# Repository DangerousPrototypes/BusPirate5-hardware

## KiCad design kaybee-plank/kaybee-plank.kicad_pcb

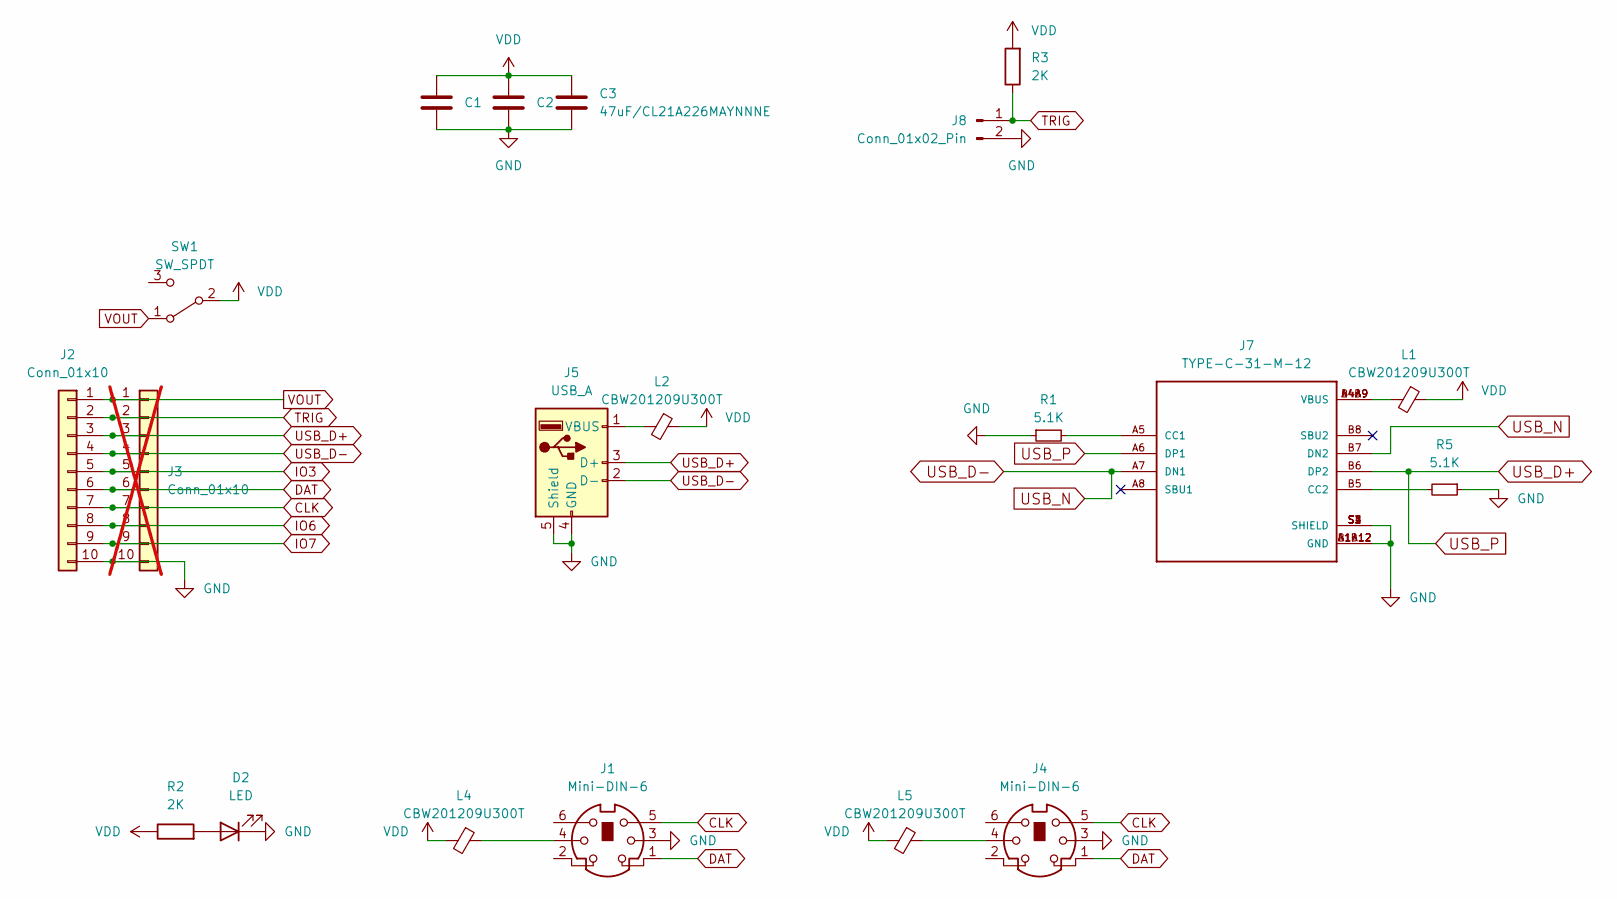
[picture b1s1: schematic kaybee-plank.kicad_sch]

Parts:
C1, C2, C3: 47uF/CL21A226MAYNNNE; C_0805_2012Metric
D2: LED; LED_0805_2012Metric
J1, J4: Mini-DIN-6; Connector_Mini-DIN_Female_6Pin_2rows
J2: Conn_01x10; PinSocket_1x10_P2.54mm_Horizontal
J3: Conn_01x10; PinHeader_1x10_P2.54mm_Vertical; not fitted
J5: USB_A; USB_A_CONNFLY_DS1095-WNR0
J7: TYPE-C-31-M-12; HRO_TYPE-C-31-M-12
J8: Conn_01x02_Pin; PinHeader_1x02_P2.54mm_Vertical
L1, L2, L4, L5: CBW201209U300T; L_0805_2012Metric
R1, R5: 5.1K; R_0805_2012Metric
R2, R3: 2K; R_0805_2012Metric
SW1: SW_SPDT; SW_SPDT_PCM12

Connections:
CLK: J1.5, J2.7, J3.7, J4.5
DAT: J1.1, J2.6, J3.6, J4.1
GND: C1.2, C2.2, C3.2, D2.1 (K), J1.3, J2.10, J3.10, J4.3, J5.4 (GND), J5.5 (Shield), J7.A1B12 (GND), J7.B1A12 (GND), J7.S1 (SHIELD), J7.S2 (SHIELD), J7.S3 (SHIELD), J7.S4 (SHIELD), J8.2, R1.1, R5.1
IO3: J2.5, J3.5
IO6: J2.8, J3.8
IO7: J2.9, J3.9
unnamed: D2.2 (A), R2.2
unnamed: J1.4, L4.1
unnamed: J4.4, L5.1
unnamed: J5.1 (VBUS), L2.2
unnamed: J7.A5 (CC1), R1.2
unnamed: J7.B5 (CC2), R5.2
unnamed: J7.A4B9 (VBUS), J7.B4A9 (VBUS), L1.2
TRIG: J2.2, J3.2, J8.1, R3.1
USB_D+: J2.3, J3.3, J5.3 (D+), J7.A6 (DP1), J7.B6 (DP2)
USB_D-: J2.4, J3.4, J5.2 (D-), J7.A7 (DN1), J7.B7 (DN2)
VDD: C1.1, C2.1, C3.1, L1.1, L2.1, L4.2, L5.2, R2.1, R3.2, SW1.2 (B)
VOUT: J2.1, J3.1, SW1.1 (A)

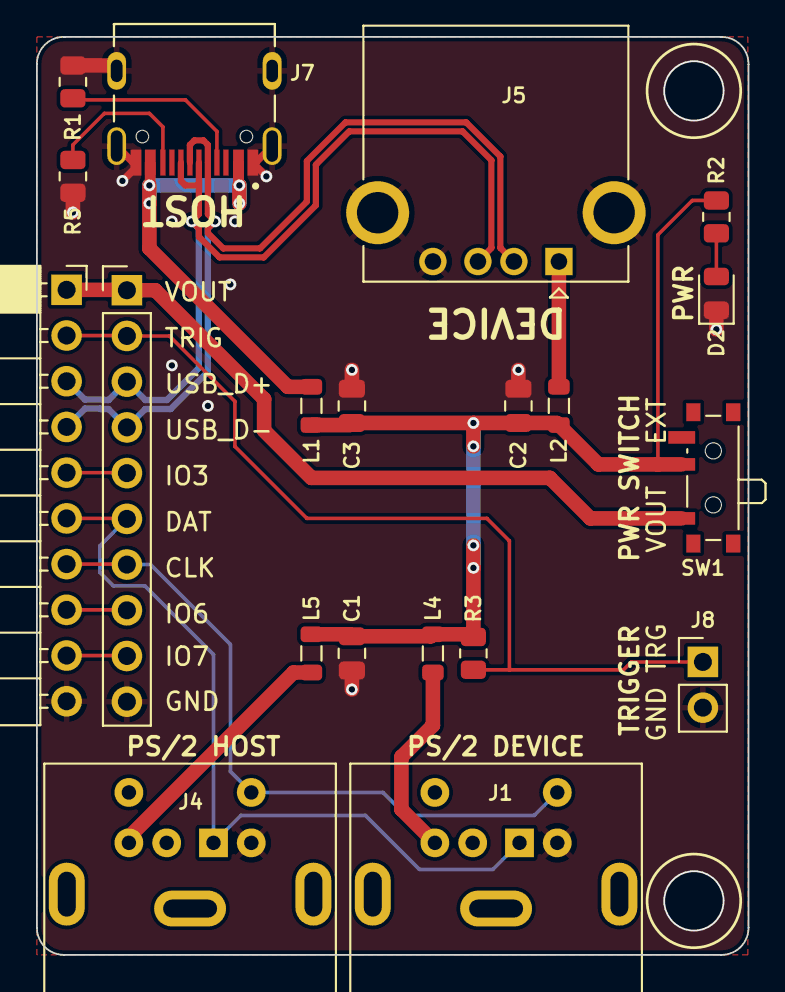
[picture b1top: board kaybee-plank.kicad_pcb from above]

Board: 2 copper layers, 39.5 x 51.0 mm, 20 parts (0 on the bottom side), 18 nets.

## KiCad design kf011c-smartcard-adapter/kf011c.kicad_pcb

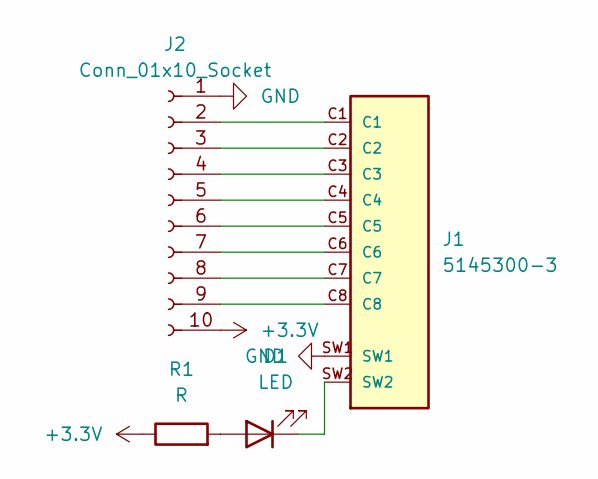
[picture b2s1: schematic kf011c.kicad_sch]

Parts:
D1: LED; LED_0805_2012Metric
J1: 5145300-3; TE_5145300-3; PARTREV C3
J2: Conn_01x10_Socket; PinHeader_1x10_P2.54mm_Horizontal
R1: R; R_0805_2012Metric

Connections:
+3.3V: J2.10, R1.1
GND: J1.SW1, J2.1
unnamed: D1.2 (A), R1.2
unnamed: D1.1 (K), J1.SW2
unnamed: J1.C1, J2.2
unnamed: J1.C2, J2.3
unnamed: J1.C3, J2.4
unnamed: J1.C4, J2.5
unnamed: J1.C5, J2.6
unnamed: J1.C6, J2.7
unnamed: J1.C7, J2.8
unnamed: J1.C8, J2.9

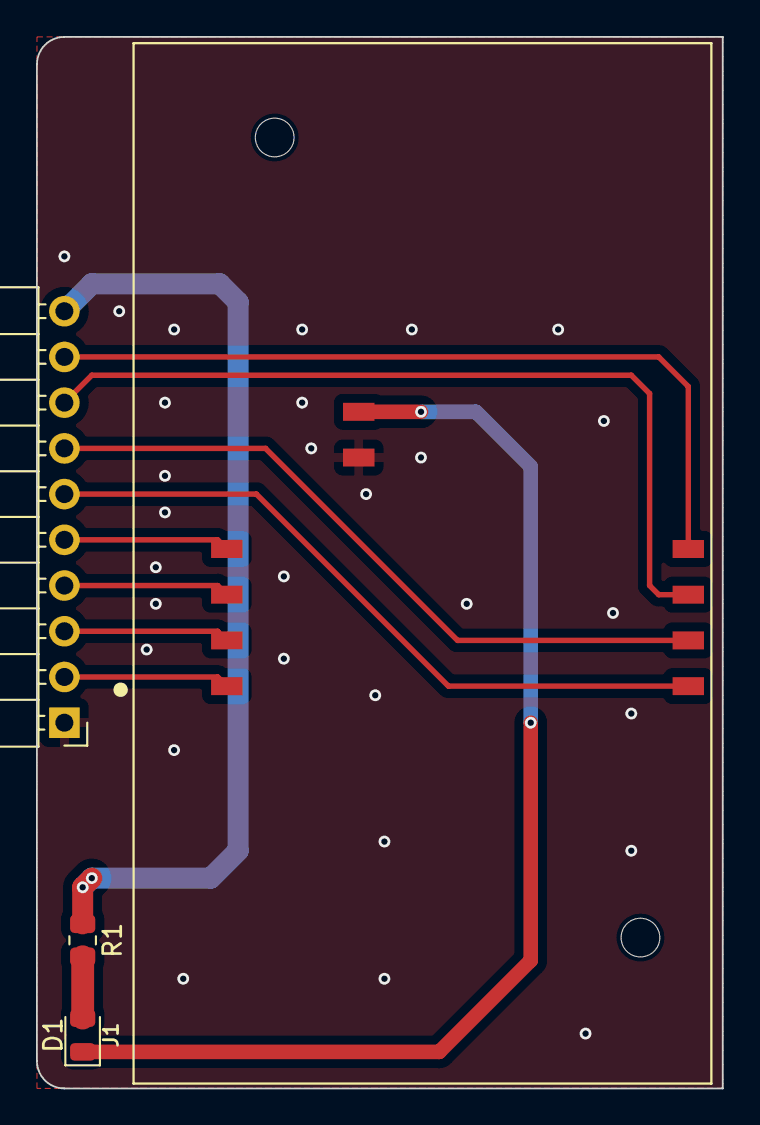
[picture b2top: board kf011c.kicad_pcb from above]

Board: 2 copper layers, 38.1 x 58.4 mm, 4 parts (0 on the bottom side), 12 nets.

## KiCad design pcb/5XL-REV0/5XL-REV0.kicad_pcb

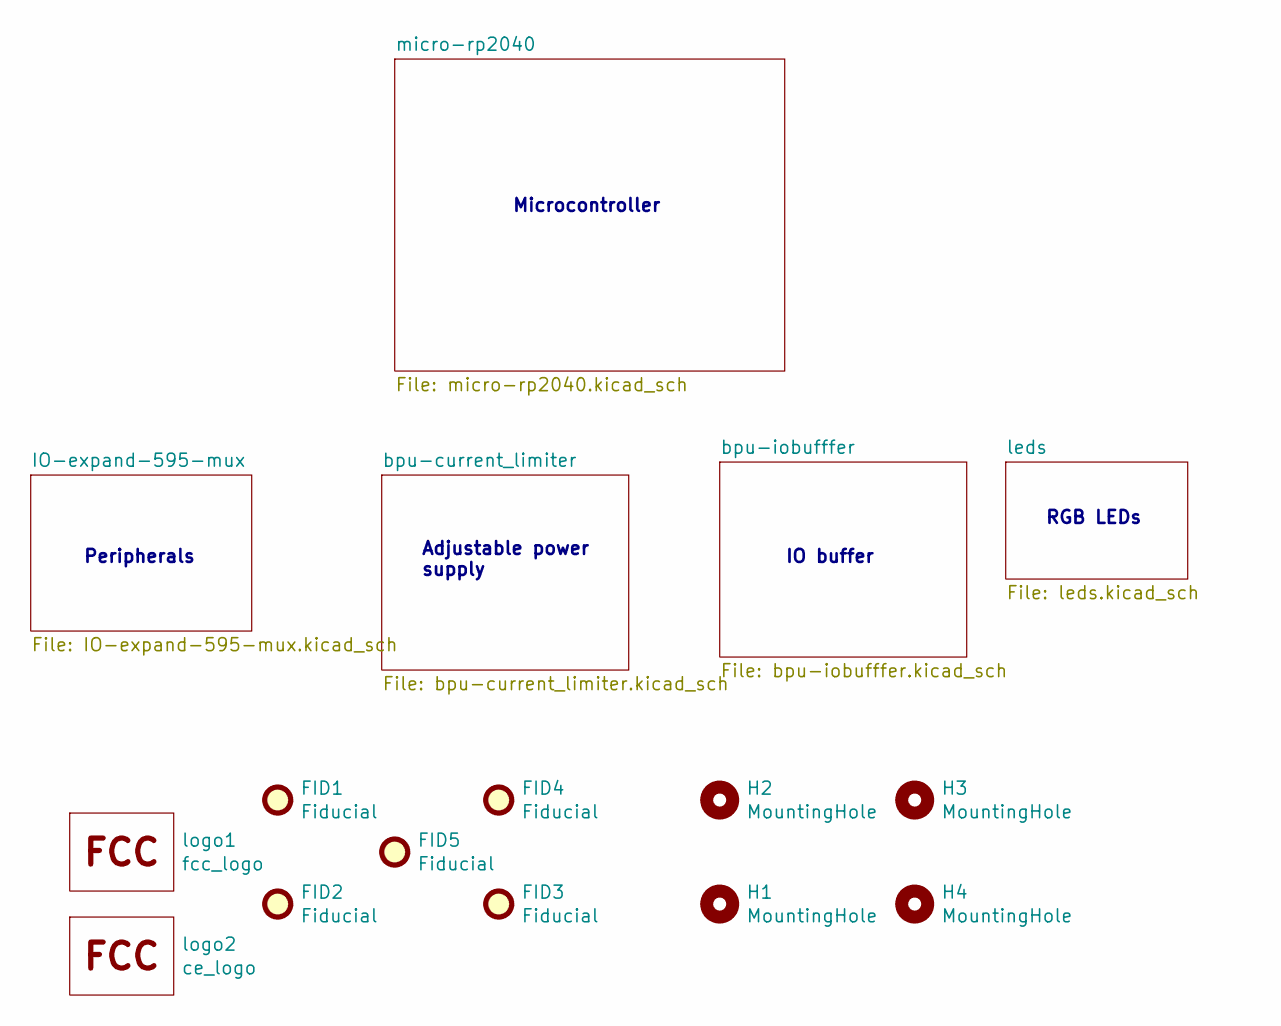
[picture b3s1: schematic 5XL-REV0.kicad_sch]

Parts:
FID1, FID2, FID3, FID4, FID5: Fiducial; Fiducial_1mm_Mask2mm
H1, H2, H3, H4: MountingHole; MountingHole_3.2mm_M3
logo1: fcc_logo; logo_fcc
logo2: ce_logo; CE-Logo_11.2x8mm_SilkScreen

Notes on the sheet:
Microcontroller
Adjustable power supply
IO buffer
Peripherals
RGB LEDs

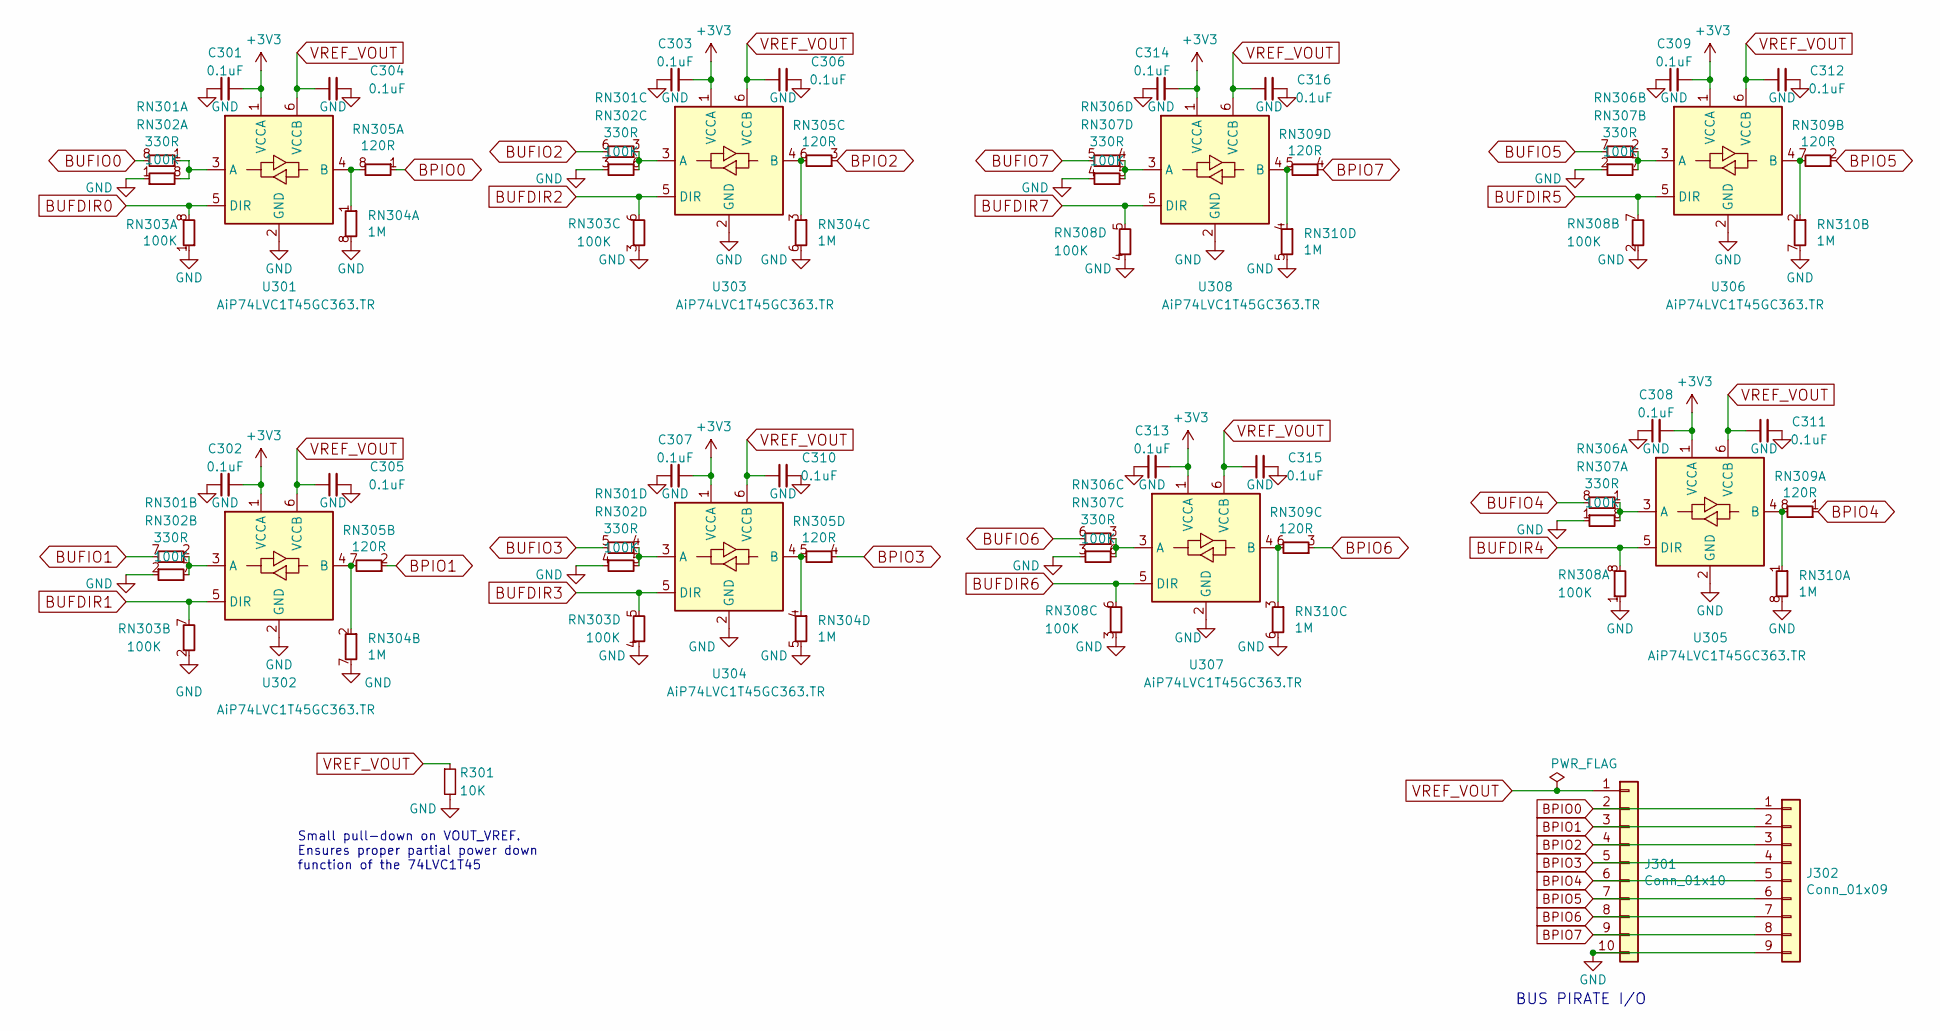
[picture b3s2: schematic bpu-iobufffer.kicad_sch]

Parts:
C301, C302, C303, C304, C305, C306, C307, C308, C309, C310, C311, C312, C313, C314, C315, C316: 0.1uF; C_0402_1005Metric
J301: Conn_01x10; PinHeader_1x10_P2.54mm_Vertical
J302: Conn_01x09; JST_SH_SM09B-SRSS-TB_1x09-1MP_P1.00mm_Horizontal
R301: 10K; R_0402_1005Metric
RN301, RN306: 330R; R_Array_Convex_4x0402
RN302, RN303, RN307, RN308: 100K; R_Array_Convex_4x0402
RN304, RN310: 1M; R_Array_Convex_4x0402
RN305, RN309: 120R; R_Array_Convex_4x0402
U301, U302, U303, U304, U305, U306, U307, U308: AiP74LVC1T45GC363.TR; SOT-363_SC-70-6

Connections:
+3V3: C301.2, C302.2, C303.2, C307.2, C308.2, C309.2, C313.2, C314.2, U301.1 (VCCA), U302.1 (VCCA), U303.1 (VCCA), U304.1 (VCCA), U305.1 (VCCA), U306.1 (VCCA), U307.1 (VCCA), U308.1 (VCCA); also elsewhere on the board
BPIO0: J301.2, J302.1, RN305.1 (R1.1); also elsewhere on the board
BPIO1: J301.3, J302.2, RN305.2 (R1.1); also elsewhere on the board
BPIO2: J301.4, J302.3, RN305.3 (R1.1); also elsewhere on the board
BPIO3: J301.5, J302.4, RN305.4 (R1.1); also elsewhere on the board
BPIO4: J301.6, J302.5, RN309.1 (R1.1); also elsewhere on the board
BPIO5: J301.7, J302.6, RN309.2 (R1.1); also elsewhere on the board
BPIO6: J301.8, J302.7, RN309.3 (R1.1); also elsewhere on the board
BPIO7: J301.9, J302.8, RN309.4 (R1.1); also elsewhere on the board
BUFDIR0: RN303.8 (R1.8), U301.5 (DIR); also elsewhere on the board
BUFDIR1: RN303.7 (R1.8), U302.5 (DIR); also elsewhere on the board
BUFDIR2: RN303.6 (R1.8), U303.5 (DIR); also elsewhere on the board
BUFDIR3: RN303.5 (R1.8), U304.5 (DIR); also elsewhere on the board
BUFDIR4: RN308.8 (R1.8), U305.5 (DIR); also elsewhere on the board
BUFDIR5: RN308.7 (R1.8), U306.5 (DIR); also elsewhere on the board
BUFDIR6: RN308.6 (R1.8), U307.5 (DIR); also elsewhere on the board
BUFDIR7: RN308.5 (R1.8), U308.5 (DIR); also elsewhere on the board
BUFIO0: RN301.8 (R1.8); also elsewhere on the board
BUFIO1: RN301.7 (R1.8); also elsewhere on the board
BUFIO2: RN301.6 (R1.8); also elsewhere on the board
BUFIO3: RN301.5 (R1.8); also elsewhere on the board
BUFIO4: RN306.8 (R1.8); also elsewhere on the board
BUFIO5: RN306.7 (R1.8); also elsewhere on the board
BUFIO6: RN306.6 (R1.8); also elsewhere on the board
BUFIO7: RN306.5 (R1.8); also elsewhere on the board
GND: C301.1, C302.1, C303.1, C304.2, C305.2, C306.2, C307.1, C308.1, C309.1, C310.2, C311.2, C312.2, C313.1, C314.1, C315.2, C316.2, J301.10, J302.9, R301.2, RN302.1 (R1.1), RN302.2 (R1.1), RN302.3 (R1.1), RN302.4 (R1.1), RN303.1 (R1.1), RN303.2 (R1.1), RN303.3 (R1.1), RN303.4 (R1.1), RN304.5 (R1.8), RN304.6 (R1.8), RN304.7 (R1.8), RN304.8 (R1.8), RN307.1 (R1.1), RN307.2 (R1.1), RN307.3 (R1.1), RN307.4 (R1.1), RN308.1 (R1.1), RN308.2 (R1.1), RN308.3 (R1.1), RN308.4 (R1.1), RN310.5 (R1.8), RN310.6 (R1.8), RN310.7 (R1.8), RN310.8 (R1.8), U301.2 (GND), U302.2 (GND), U303.2 (GND), U304.2 (GND), U305.2 (GND), U306.2 (GND), U307.2 (GND), U308.2 (GND); also elsewhere on the board
unnamed: RN301.1 (R1.1), RN302.8 (R1.8), U301.3 (A)
unnamed: RN301.2 (R1.1), RN302.7 (R1.8), U302.3 (A)
unnamed: RN301.3 (R1.1), RN302.6 (R1.8), U303.3 (A)
unnamed: RN301.4 (R1.1), RN302.5 (R1.8), U304.3 (A)
unnamed: RN304.1 (R1.1), RN305.8 (R1.8), U301.4 (B)
unnamed: RN304.2 (R1.1), RN305.7 (R1.8), U302.4 (B)
unnamed: RN304.3 (R1.1), RN305.6 (R1.8), U303.4 (B)
unnamed: RN304.4 (R1.1), RN305.5 (R1.8), U304.4 (B)
unnamed: RN306.1 (R1.1), RN307.8 (R1.8), U305.3 (A)
unnamed: RN306.2 (R1.1), RN307.7 (R1.8), U306.3 (A)
unnamed: RN306.3 (R1.1), RN307.6 (R1.8), U307.3 (A)
unnamed: RN306.4 (R1.1), RN307.5 (R1.8), U308.3 (A)
unnamed: RN309.8 (R1.8), RN310.1 (R1.1), U305.4 (B)
unnamed: RN309.7 (R1.8), RN310.2 (R1.1), U306.4 (B)
unnamed: RN309.6 (R1.8), RN310.3 (R1.1), U307.4 (B)
unnamed: RN309.5 (R1.8), RN310.4 (R1.1), U308.4 (B)
VREF_VOUT: C304.1, C305.1, C306.1, C310.1, C311.1, C312.1, C315.1, C316.1, J301.1, R301.1, U301.6 (VCCB), U302.6 (VCCB), U303.6 (VCCB), U304.6 (VCCB), U305.6 (VCCB), U306.6 (VCCB), U307.6 (VCCB), U308.6 (VCCB); also elsewhere on the board

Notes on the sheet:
Small pull-down on VOUT_VREF. Ensures proper partial power down function of the 74LVC1T45
BUS PIRATE I/O

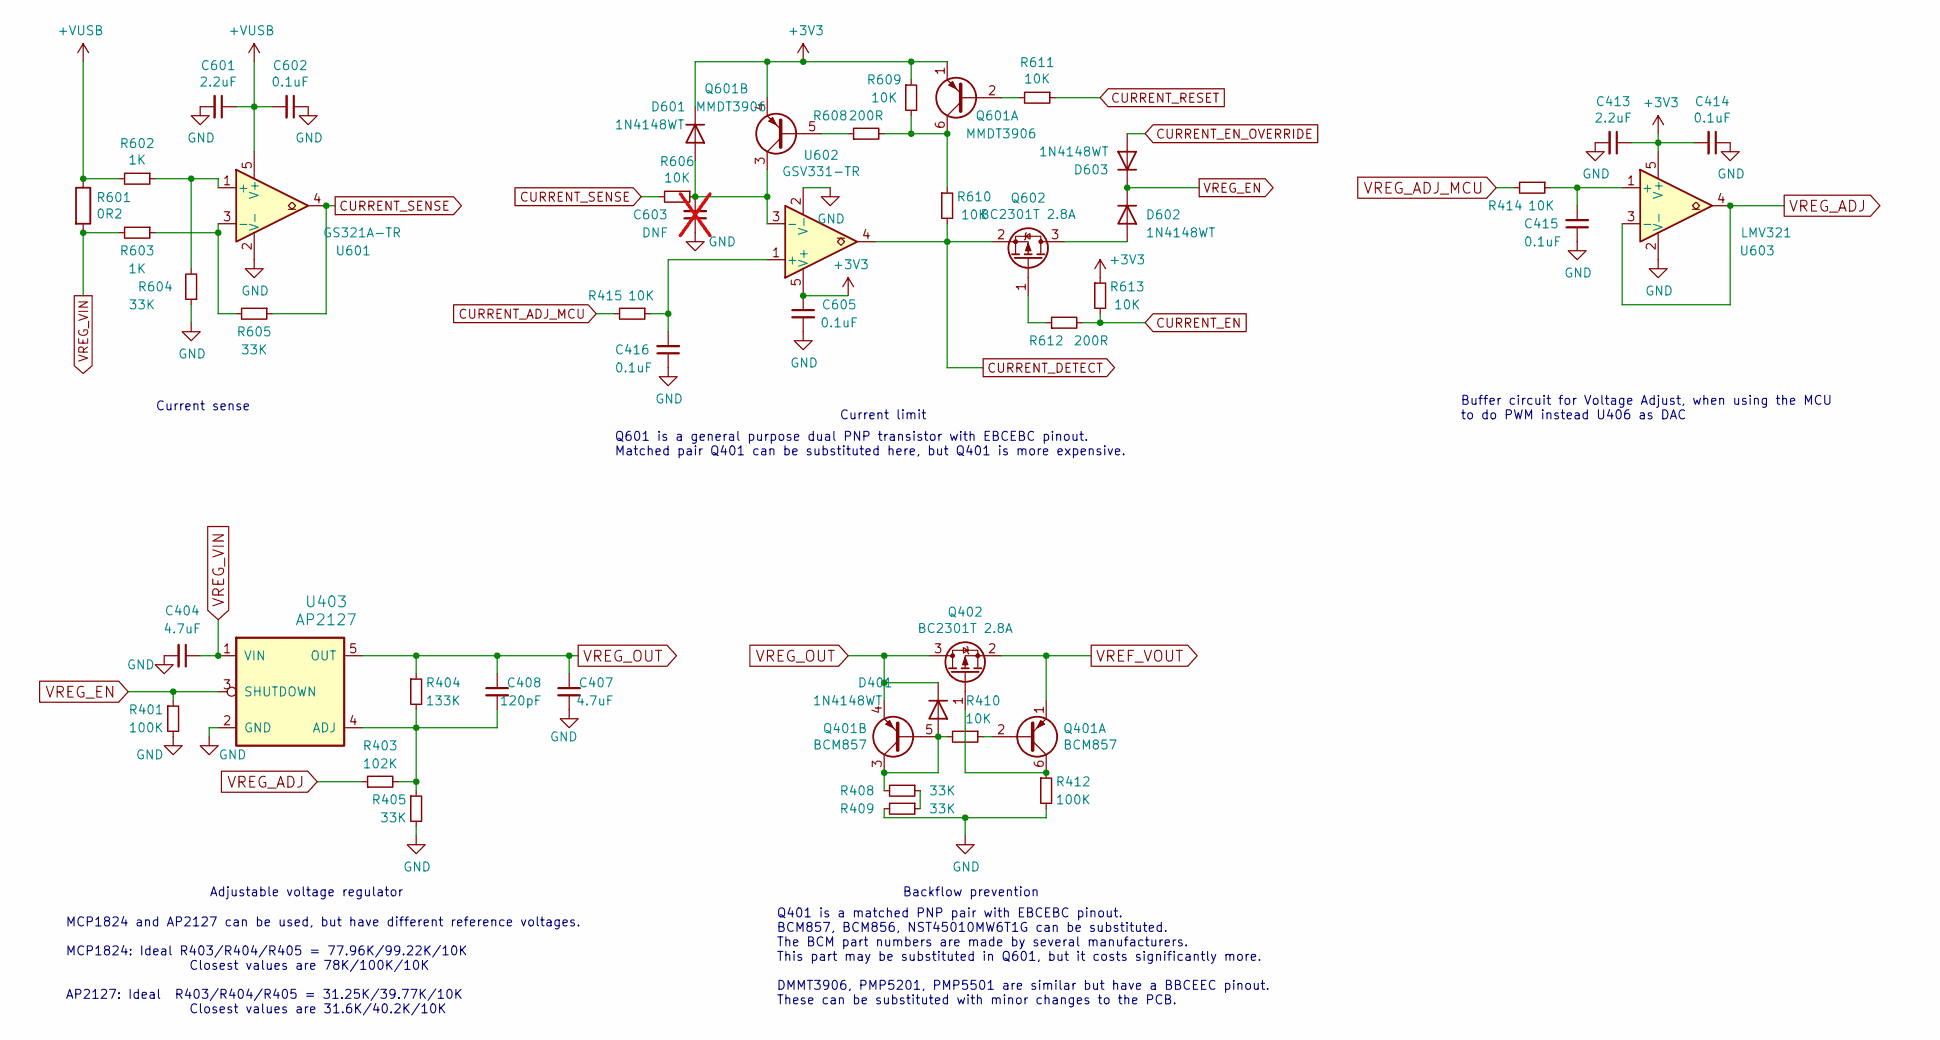
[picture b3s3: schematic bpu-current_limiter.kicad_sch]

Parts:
C404, C407: 4.7uF; C_0402_1005Metric
C408: 120pF; C_0402_1005Metric
C413, C601: 2.2uF; C_0402_1005Metric
C414, C415, C416, C602, C605: 0.1uF; C_0402_1005Metric
C603: DNF; C_0402_1005Metric; not fitted
D401, D601, D602, D603: 1N4148WT; D_SOD-523
Q401: BCM857; SOT-363_SC-70-6
Q402, Q602: BC2301T 2.8A; SOT-523
Q601: MMDT3906; SOT-363_SC-70-6
R401, R412: 100K; R_0402_1005Metric
R403: 102K; R_0402_1005Metric
R404: 133K; R_0402_1005Metric
R405, R408, R409, R604, R605: 33K; R_0402_1005Metric
R410, R414, R415, R606, R609, R610, R611, R613: 10K; R_0402_1005Metric
R601: 0R2; R_2512_6332Metric_Pad1.40x3.35mm_HandSolder
R602, R603: 1K; R_0402_1005Metric
R608, R612: 200R; R_0402_1005Metric
U403: AP2127; SOT-23-5
U601: GS321A-TR; SOT-23-5
U602: GSV331-TR; SOT-23-5
U603: LMV321; SOT-23-5

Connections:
+3V3: C413.1, C414.2, C605.1, D601.1 (K), Q601.1 (E1), Q601.4 (E2), R609.1, R613.1, U602.5 (V+), U603.5 (V+); also elsewhere on the board
+VUSB: C601.1, C602.2, R601.1, R602.2, U601.5 (V+); also elsewhere on the board
CURRENT_ADJ_MCU: R415.2; also elsewhere on the board
CURRENT_DETECT: Q602.2 (S), R610.2, U602.4; also elsewhere on the board
CURRENT_EN: R612.2, R613.2; also elsewhere on the board
CURRENT_EN_OVERRIDE: D603.2 (A); also elsewhere on the board
CURRENT_RESET: R611.1; also elsewhere on the board
CURRENT_SENSE: R605.1, R606.2, U601.4; also elsewhere on the board
GND: C404.2, C407.2, C413.2, C414.1, C415.1, C416.1, C601.2, C602.1, C603.1, C605.2, R401.2, R405.2, R409.2, R412.2, R604.1, U403.2 (GND), U601.2 (V-), U602.2 (V-), U603.2 (V-); also elsewhere on the board
unnamed: D401.2 (A), Q401.3 (C2), Q401.5 (B2), R408.2, R410.2
unnamed: C603.2, D601.2 (A), Q601.3 (C2), R606.1, U602.3 (-)
unnamed: D602.2 (A), Q602.3 (D)
unnamed: Q401.2 (B1), R410.1
unnamed: Q401.6 (C1), Q402.1 (G), R412.1
unnamed: Q601.2 (B1), R611.2
unnamed: Q601.6 (C1), R608.2, R609.2, R610.1
unnamed: Q601.5 (B2), R608.1
unnamed: Q602.1 (G), R612.1
unnamed: R408.1, R409.1
unnamed: C408.2, R403.2, R404.2, R405.1, U403.4 (ADJ)
unnamed: R602.1, R604.2, U601.1 (+)
unnamed: R603.1, R605.2, U601.3 (-)
unnamed: C416.2, R415.1, U602.1 (+)
unnamed: C415.2, R414.1, U603.1 (+)
VREF_VOUT: Q401.1 (E1), Q402.2 (S); also elsewhere on the board
VREG_ADJ: R403.1, U603.3 (-), U603.4
VREG_ADJ_MCU: R414.2; also elsewhere on the board
VREG_EN: D602.1 (K), D603.1 (K), R401.1, U403.3 (SHUTDOWN)
VREG_OUT: C407.1, C408.1, D401.1 (K), Q401.4 (E2), Q402.3 (D), R404.1, U403.5 (OUT); also elsewhere on the board
VREG_VIN: C404.1, R601.2, R603.2, U403.1 (VIN)

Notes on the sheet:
Adjustable voltage regulator
Buffer circuit for Voltage Adjust, when using the MCU to do PWM instead U406 as DAC
Current sense
Backflow prevention
MCP1824 and AP2127 can be used, but have different reference voltages. MCP1824: Ideal R403/R404/R405 = 77.96K/99.22K/10K Closest values are 78K/100K/10K AP2127: Ideal R403/R404/R405 = 31.25K/39.77K/10K Closest values are 31.6K/40.2K/10K
Current limit
Q401 is a matched PNP pair with EBCEBC pinout. BCM857, BCM856, NST45010MW6T1G can be substituted. The BCM part numbers are made by several manufacturers. This part may be substituted in Q601, but it costs significantly more. DMMT3906, PMP5201, PMP5501 are similar but have a BBCEEC pinout. These can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
Q601 is a general purpose dual PNP transistor with EBCEBC pinout. Matched pair Q401 can be substituted here, but Q401 is more expensive.

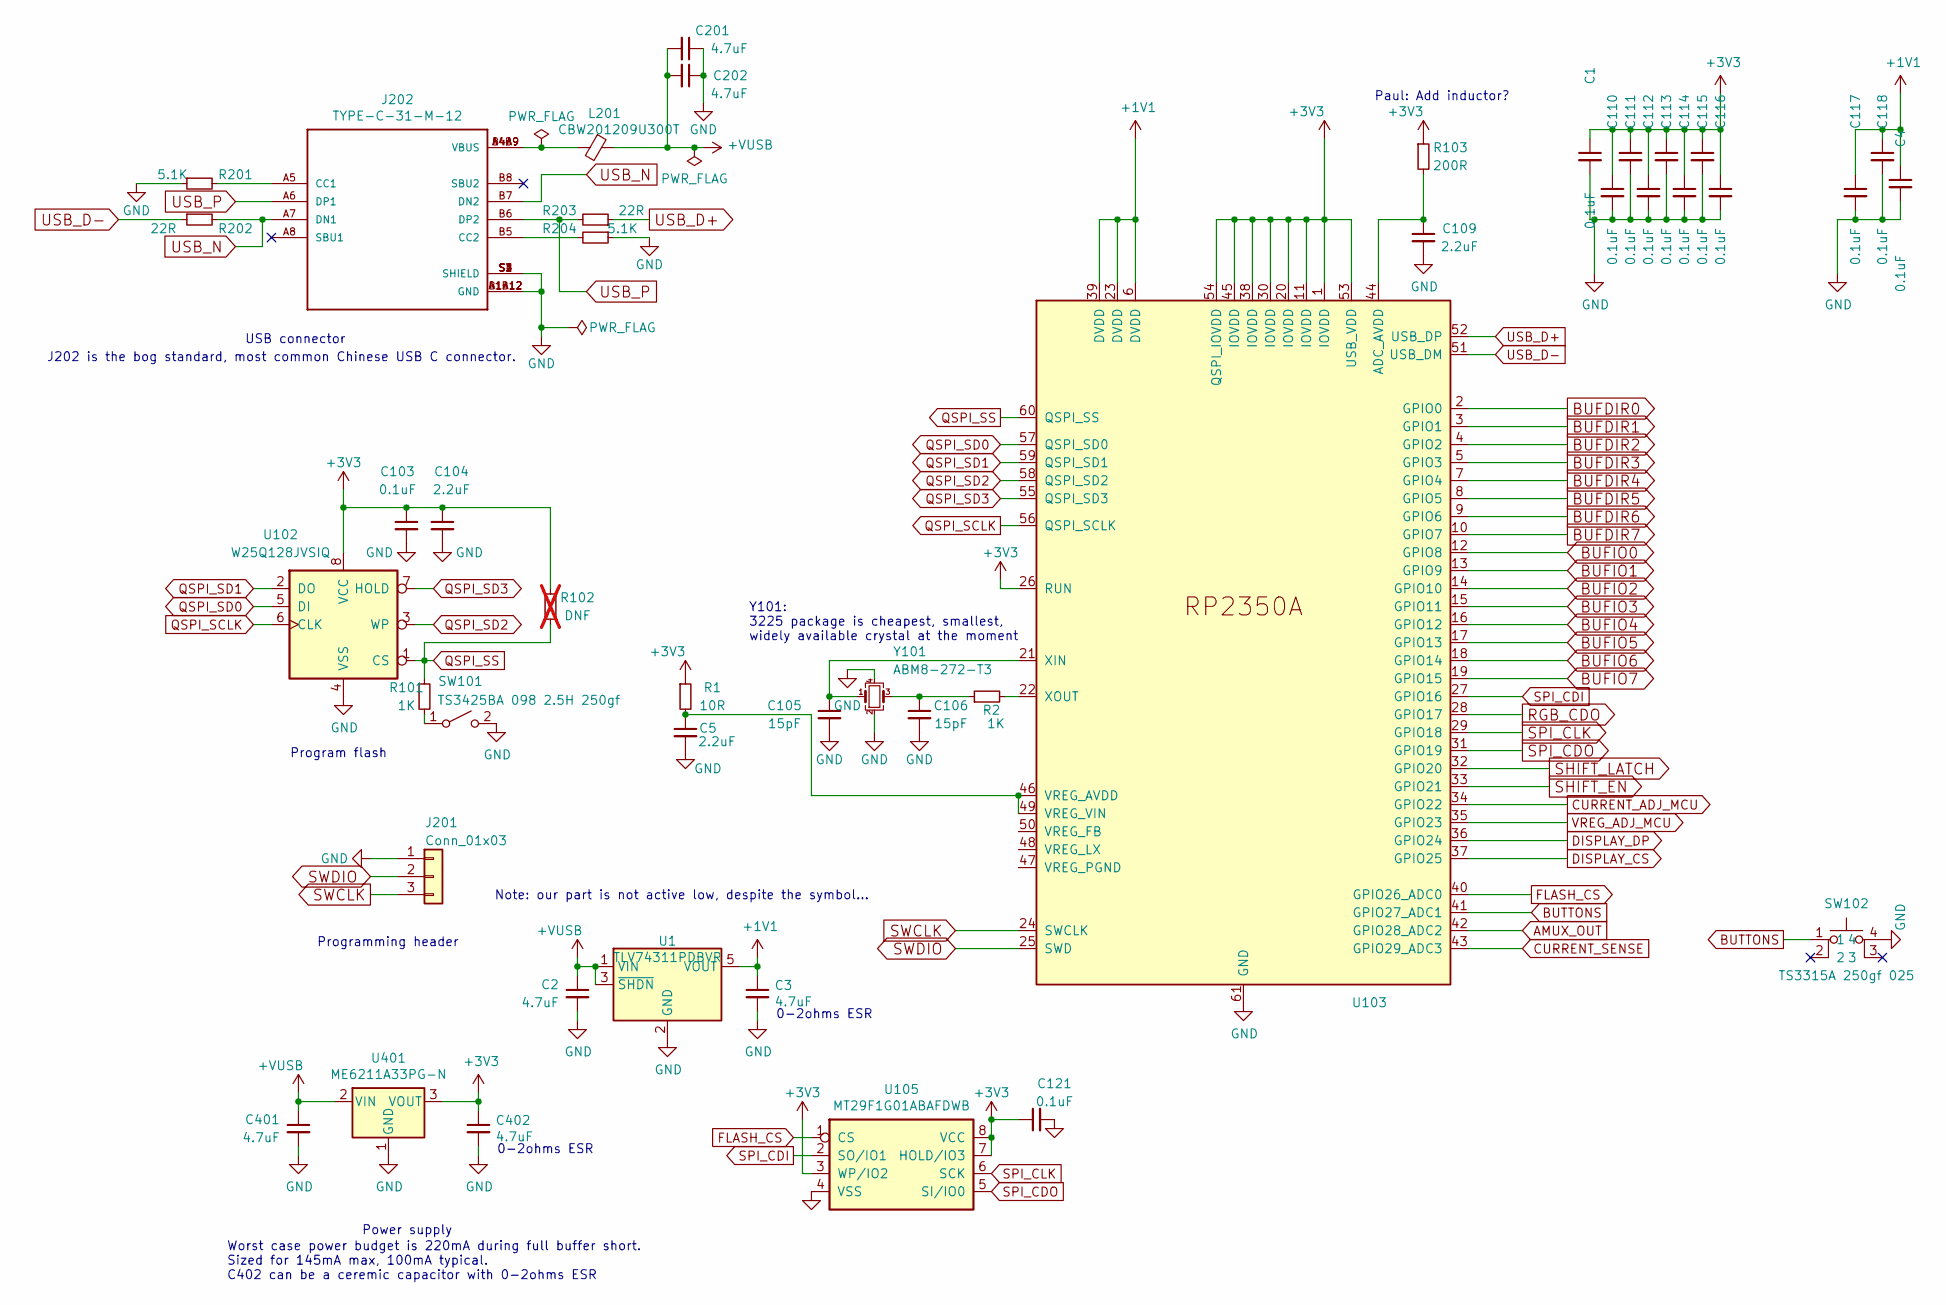
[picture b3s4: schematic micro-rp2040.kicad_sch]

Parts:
C1, C4, C103, C110, C111, C112, C113, C114, C115, C116, C117, C118, C121: 0.1uF; C_0402_1005Metric
C2, C3, C201, C202, C401, C402: 4.7uF; C_0402_1005Metric
C5, C104, C109: 2.2uF; C_0402_1005Metric
C105, C106: 15pF; C_0402_1005Metric
J201: Conn_01x03; PinSocket_1x03_P2.54mm_Vertical
J202: TYPE-C-31-M-12; HRO_TYPE-C-31-M-12
L201: CBW201209U300T; L_0805_2012Metric
R1: 10R; R_0402_1005Metric
R2, R101: 1K; R_0402_1005Metric
R102: DNF; R_0402_1005Metric; not fitted
R103: 200R; R_0402_1005Metric
R201, R204: 5.1K; R_0402_1005Metric
R202, R203: 22R; R_0402_1005Metric
SW101: TS3425BA 098 2.5H 250gf; SW_SPST_PTS810
SW102: TS3315A 250gf 025; GT-TC026X-HXXX-LX
U1: TLV74311PDBVR; SOT-23-5
U102: W25Q128JVSIQ; SOP-8_5.28x5.23mm_P1.27mm
U103: RP2350A; QFN40P700X700X80-61N-D
U105: MT29F1G01ABAFDWB; U-PDFN-8
U401: ME6211A33PG-N; SOT-89-3
Y101: ABM8-272-T3; Crystal_SMD_3225-4Pin_3.2x2.5mm

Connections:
+1V1: C3.1, C4.1, C117.1, C118.1, U1.5 (VOUT), U103.6 (DVDD), U103.23 (DVDD), U103.39 (DVDD)
+3V3: C1.1, C103.1, C104.1, C110.1, C111.1, C112.1, C113.1, C114.1, C115.1, C116.1, C121.1, C402.1, R1.1, R102.1, R103.1, U102.8 (VCC), U103.1 (IOVDD), U103.11 (IOVDD), U103.20 (IOVDD), U103.26 (RUN), U103.30 (IOVDD), U103.38 (IOVDD), U103.45 (IOVDD), U103.53 (USB_VDD), U103.54 (QSPI_IOVDD), U105.3 (WP/IO2), U105.7 (HOLD/IO3), U105.8 (VCC), U401.3 (VOUT); also elsewhere on the board
+VUSB: C2.1, C201.2, C202.2, C401.1, L201.1, U1.1 (VIN), U1.3 (~SHDN), U401.2 (VIN); also elsewhere on the board
AMUX_OUT: U103.42 (GPIO28_ADC2); also elsewhere on the board
BUFDIR0: U103.2 (GPIO0); also elsewhere on the board
BUFDIR1: U103.3 (GPIO1); also elsewhere on the board
BUFDIR2: U103.4 (GPIO2); also elsewhere on the board
BUFDIR3: U103.5 (GPIO3); also elsewhere on the board
BUFDIR4: U103.7 (GPIO4); also elsewhere on the board
BUFDIR5: U103.8 (GPIO5); also elsewhere on the board
BUFDIR6: U103.9 (GPIO6); also elsewhere on the board
BUFDIR7: U103.10 (GPIO7); also elsewhere on the board
BUFIO0: U103.12 (GPIO8); also elsewhere on the board
BUFIO1: U103.13 (GPIO9); also elsewhere on the board
BUFIO2: U103.14 (GPIO10); also elsewhere on the board
BUFIO3: U103.15 (GPIO11); also elsewhere on the board
BUFIO4: U103.16 (GPIO12); also elsewhere on the board
BUFIO5: U103.17 (GPIO13); also elsewhere on the board
BUFIO6: U103.18 (GPIO14); also elsewhere on the board
BUFIO7: U103.19 (GPIO15); also elsewhere on the board
BUTTONS: SW102.1, U103.41 (GPIO27_ADC1)
CURRENT_ADJ_MCU: U103.34 (GPIO22); also elsewhere on the board
CURRENT_SENSE: U103.43 (GPIO29_ADC3); also elsewhere on the board
DISPLAY_CS: U103.37 (GPIO25); also elsewhere on the board
DISPLAY_DP: U103.36 (GPIO24); also elsewhere on the board
FLASH_CS: U103.40 (GPIO26_ADC0), U105.1 (CS)
GND: C1.2, C2.2, C3.2, C4.2, C5.2, C103.2, C104.2, C105.2, C106.2, C109.2, C110.2, C111.2, C112.2, C113.2, C114.2, C115.2, C116.2, C117.2, C118.2, C121.2, C201.1, C202.1, C401.2, C402.2, J201.1, J202.A1B12 (GND), J202.B1A12 (GND), J202.S1 (SHIELD), J202.S2 (SHIELD), J202.S3 (SHIELD), J202.S4 (SHIELD), R201.1, R204.1, SW101.2 (B), SW102.4, U1.2 (GND), U102.4 (VSS), U103.61 (GND), U105.4 (VSS), U401.1 (GND), Y101.2, Y101.4; also elsewhere on the board
unnamed: C106.1, R2.1, Y101.3
unnamed: J202.A5 (CC1), R201.2
unnamed: J202.B5 (CC2), R204.2
unnamed: J202.A4B9 (VBUS), J202.B4A9 (VBUS), L201.2
unnamed: R101.2, SW101.1 (A)
unnamed: C109.1, R103.2, U103.44 (ADC_AVDD)
unnamed: C5.1, R1.2, U103.46 (VREG_AVDD), U103.49 (VREG_VIN)
unnamed: C105.1, U103.21 (XIN), Y101.1
unnamed: R2.2, U103.22 (XOUT)
QSPI_SCLK: U102.6 (CLK), U103.56 (QSPI_SCLK)
QSPI_SD0: U102.5 (DI), U103.57 (QSPI_SD0)
QSPI_SD1: U102.2 (DO), U103.59 (QSPI_SD1)
QSPI_SD2: U102.3 (WP), U103.58 (QSPI_SD2)
QSPI_SD3: U102.7 (HOLD), U103.55 (QSPI_SD3)
QSPI_SS: R101.1, R102.2, U102.1 (CS), U103.60 (QSPI_SS)
RGB_CDO: U103.28 (GPIO17); also elsewhere on the board
SHIFT_EN: U103.33 (GPIO21); also elsewhere on the board
SHIFT_LATCH: U103.32 (GPIO20); also elsewhere on the board
SPI_CDI: U103.27 (GPIO16), U105.2 (SO/IO1)
SPI_CDO: U103.31 (GPIO19), U105.5 (SI/IO0); also elsewhere on the board
SPI_CLK: U103.29 (GPIO18), U105.6 (SCK); also elsewhere on the board
SWCLK: J201.3, U103.24 (SWCLK)
SWDIO: J201.2, U103.25 (SWD)
USB_D+: R203.1, U103.52 (USB_DP)
USB_D-: R202.1, U103.51 (USB_DM)
USB_N: J202.A7 (DN1), J202.B7 (DN2), R202.2
USB_P: J202.A6 (DP1), J202.B6 (DP2), R203.2
VREG_ADJ_MCU: U103.35 (GPIO23); also elsewhere on the board

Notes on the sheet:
0-2ohms ESR
USB connector
Y101: 3225 package is cheapest, smallest, widely available crystal at the moment
Power supply
J202 is the bog standard, most common Chinese USB C connector.
Program flash
Worst case power budget is 220mA during full buffer short. Sized for 145mA max, 100mA typical. C402 can be a ceremic capacitor with 0-2ohms ESR
Paul: Add inductor?
Note: our part is not active low, despite the symbol...
Programming header
